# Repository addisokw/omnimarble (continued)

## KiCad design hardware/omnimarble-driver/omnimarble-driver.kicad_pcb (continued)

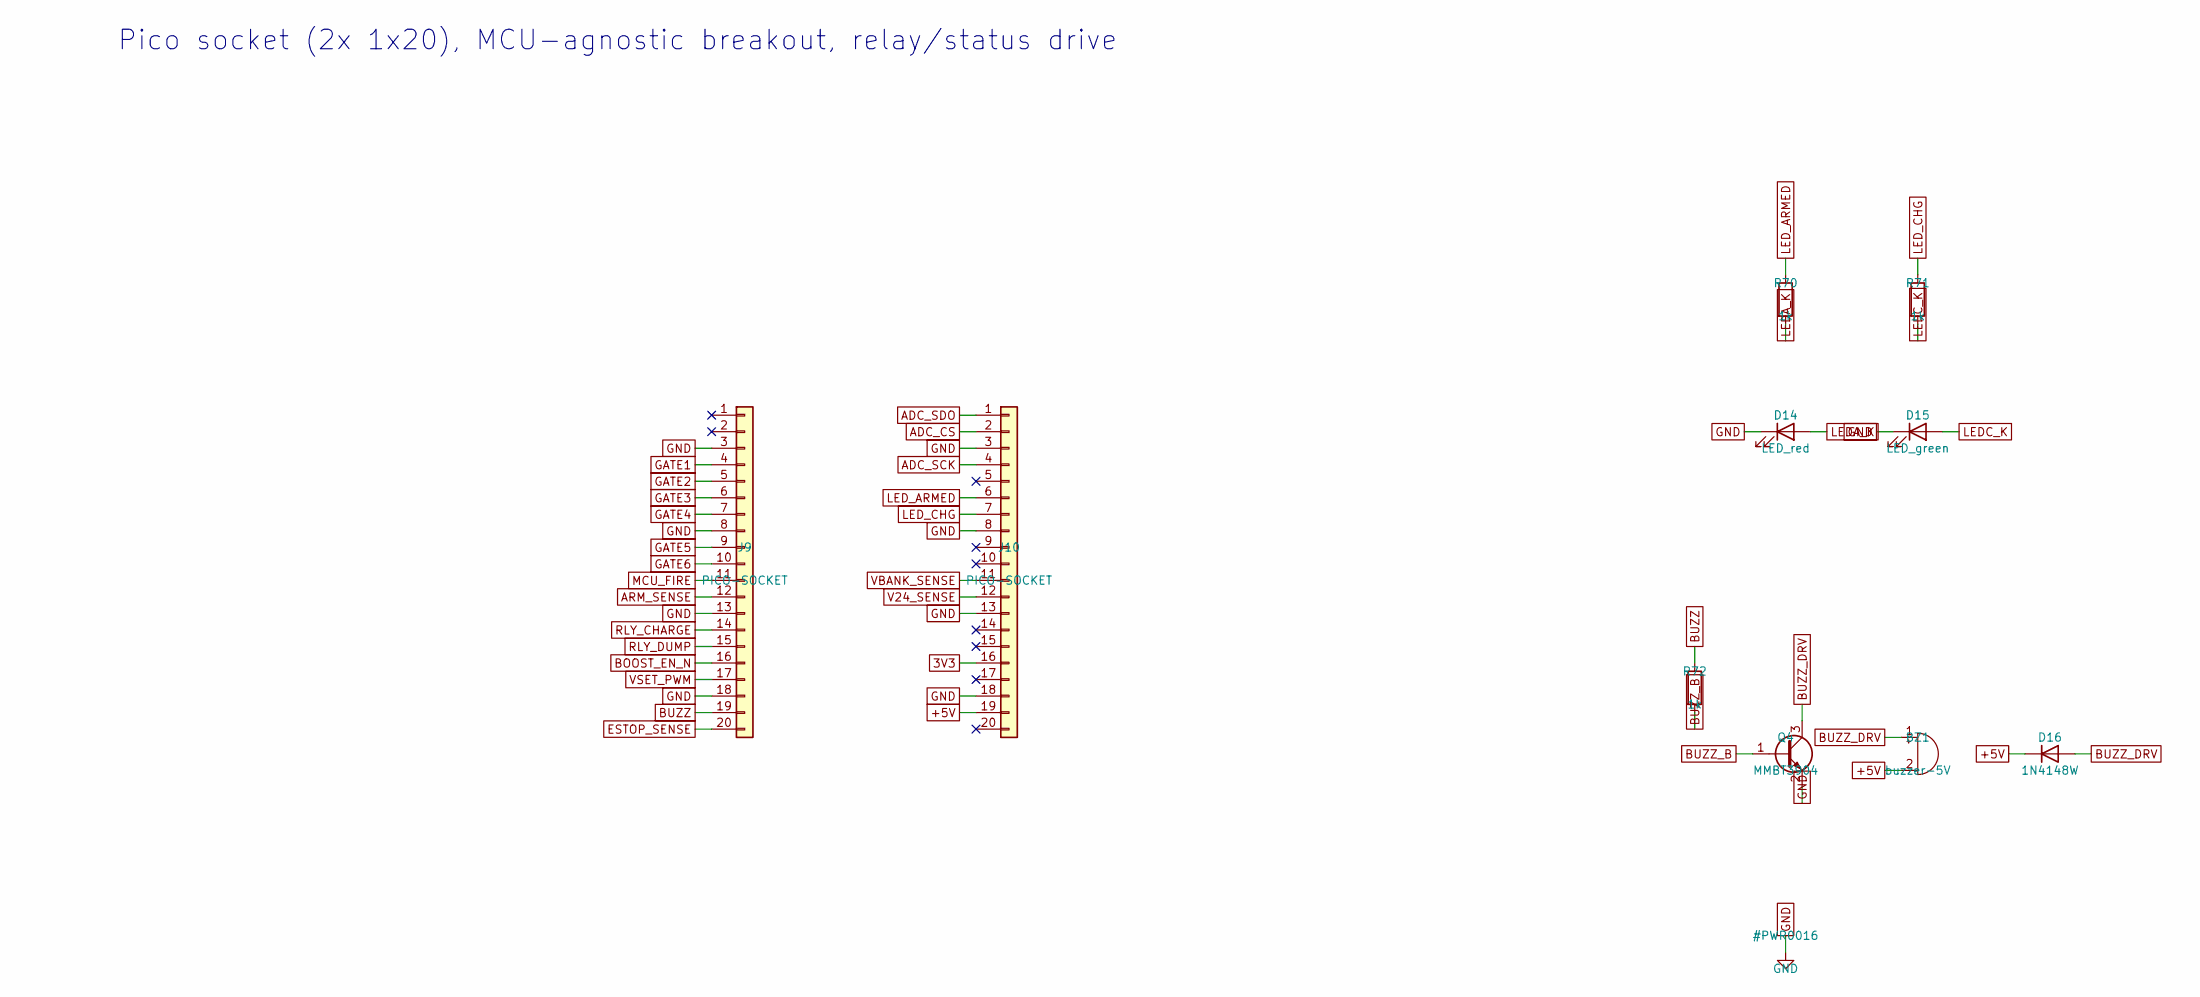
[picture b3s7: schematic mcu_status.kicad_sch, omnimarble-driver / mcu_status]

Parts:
BZ1: buzzer-5V; Buzzer_12x9.5RM7.6; LCSC C409842
D14: LED_red; LED_0603_1608Metric; LCSC C2286
D15: LED_green; LED_0603_1608Metric; LCSC C72043
D16: 1N4148W; D_SOD-123; LCSC C81598
J9, J10: PICO-SOCKET; PinSocket_1x20_P2.54mm_Vertical; LCSC C50984
Q4: MMBT3904; SOT-23; LCSC C20526
R70, R71, R72: 1k; R_0603_1608Metric; LCSC C21190

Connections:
3V3: J10.16; also elsewhere on the board
+5V: BZ1.2 (-), D16.1 (K), J10.19; also elsewhere on the board
ADC_CS: J10.2; also elsewhere on the board
ADC_SCK: J10.4; also elsewhere on the board
ADC_SDO: J10.1; also elsewhere on the board
ARM_SENSE: J9.12; also elsewhere on the board
BOOST_EN_N: J9.16; also elsewhere on the board
BUZZ: J9.19, R72.1
BUZZ_B: Q4.1 (B), R72.2
BUZZ_DRV: BZ1.1 (+), D16.2 (A), Q4.3 (C)
ESTOP_SENSE: J9.20; also elsewhere on the board
GATE1: J9.4; also elsewhere on the board
GATE2: J9.5; also elsewhere on the board
GATE3: J9.6; also elsewhere on the board
GATE4: J9.7; also elsewhere on the board
GATE5: J9.9; also elsewhere on the board
GATE6: J9.10; also elsewhere on the board
GND: D14.1 (K), D15.1 (K), J9.3, J9.8, J9.13, J9.18, J10.3, J10.8, J10.13, J10.18, Q4.2 (E); also elsewhere on the board
LEDA_K: D14.2 (A), R70.2
LEDC_K: D15.2 (A), R71.2
LED_ARMED: J10.6, R70.1
LED_CHG: J10.7, R71.1
MCU_FIRE: J9.11; also elsewhere on the board
RLY_CHARGE: J9.14; also elsewhere on the board
RLY_DUMP: J9.15; also elsewhere on the board
V24_SENSE: J10.12; also elsewhere on the board
VBANK_SENSE: J10.11; also elsewhere on the board
VSET_PWM: J9.17; also elsewhere on the board

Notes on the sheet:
Pico socket (2x 1x20), MCU-agnostic breakout, relay/status drive

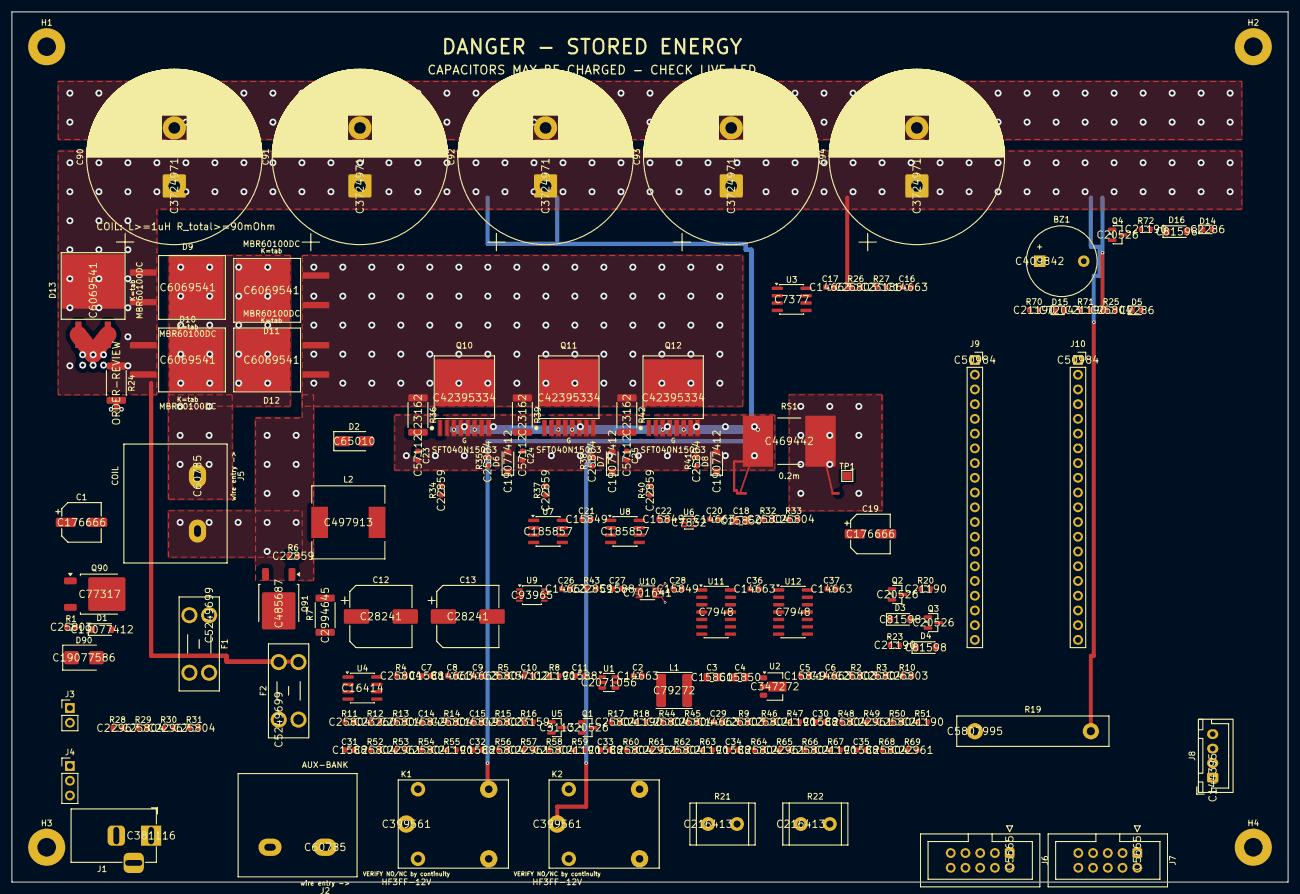
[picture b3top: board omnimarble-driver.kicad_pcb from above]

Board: 4 copper layers, 220.0 x 150.0 mm, 177 parts (0 on the bottom side), 95 nets.

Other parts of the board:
H1, H2, H3, H4: MountingHole_3.2mm_M3_Pad

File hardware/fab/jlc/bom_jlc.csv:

Comment,Designator,Footprint,LCSC Part #,Qty
10k,"R3,R4,R5,R11,R13,R14,R17,R29,R31,R32,R33,R35,R38,R41,R44,R45,R46,R48,R50,R52,R54,R56,R58,R60,R62,R64,R66,R68",R_0603_1608Metric,C25804,28
1k,"R8,R18,R20,R23,R47,R51,R55,R59,R63,R67,R70,R71,R72",R_0603_1608Metric,C21190,13
100n,"C2,C6,C8,C9,C16,C17,C20,C26,C29,C36,C37",C_0603_1608Metric,C14663,11
1n,"C7,C11,C27,C30,C31,C32,C33,C34,C35",C_0603_1608Metric,C1588,9
100k,"R1,R2,R9,R10,R15,R26",R_0603_1608Metric,C25803,6
1u,"C5,C14,C15,C21,C22,C28",C_0603_1608Metric,C15849,6
220k,"R49,R53,R57,R61,R65,R69",R_0603_1608Metric,C22961,6
10R,"R6,R34,R37,R40,R43",R_0603_1608Metric,C22859,5
MBR60100DC,"D9,D10,D11,D12,D13",D2PAK_MBR60100DC,C6069541,5
10n,"C10,C23,C24,C25",C_0603_1608Metric,C57112,4
BZT52C15,"D1,D6,D7,D8",D_SOD-123,C19077412,4
MMBT3904,"Q1,Q2,Q3,Q4",SOT-23,C20526,4
10u,"C3,C4,C18",C_0805_2012Metric,C15850,3
1N4148W,"D3,D4,D16",D_SOD-123,C81598,3
4.7R,"R36,R39,R42",R_2512_6332Metric,C25489,3
SFT040N150C3,"Q10,Q11,Q12",TOLL-8,C42395334,3
100R-10W,"R21,R22",R_Radial_Power_L11.0mm_W7.0mm_P5.00mm,C5110275,2
100u-35V,"C1,C19",CP_Elec_6.3x7.7,C176666,2
100u-63V,"C12,C13",CP_Elec_10x10.5,C28241,2
27k,"R28,R30",R_0603_1608Metric,C22967,2
HF3FF-12V,"K1,K2",Relay_HF3FF_T73,C399561,2
LED_red,"D5,D14",LED_0603_1608Metric,C2286,2
LM339,"U11,U12",SOIC-14_3.9x8.7mm_P1.27mm,C7948,2
UCC27524A,"U7,U8",SOIC-8_3.9x4.9mm_P1.27mm,C185857,2
0.15R-2512,R7,R_2512_6332Metric,C2903485,1
0.2m,RS1,Shunt_5930,C469442,1
10uH,L1,L_Changjiang_FNR6045S,C79272,1
24V-IN,J1,BarrelJack_Horizontal,C381116,1
4.3k,R16,R_0603_1608Metric,C23159,1
47R-5W,R19,R_Box_L26.0mm_W5.0mm_P20.00mm,C5807995,1
47k,R25,R_0603_1608Metric,C25819,1
47uH,L2,L_12x12mm_H8mm,C497913,1
5.1k,R27,R_0603_1608Metric,C23186,1
6.8k,R24,R_2512_6332Metric,C26073,1
74LVC1G08,U6,SOT-353_SC-70-5,C7832,1
78L12,U2,SOT-89-3,C347272,1
9.1k,R12,R_0603_1608Metric,C23260,1
ADS7042,U10,VSSOP-8_2.3x2mm_P0.5mm,C701641,1
AOD4185,Q90,TO-252-2,C5371006,1
AOD66923,Q91,TO-252-2,C485687,1
AP63205,U1,TSOT-23-6,C2071056,1
AUX-BANK,J2,TerminalBarrier_1x02_P9.50mm,C707836,1
COIL,J5,TerminalBarrier_1x02_P9.50mm,C707836,1
INA240A1,U9,TSSOP-8_3x3mm_P0.65mm,C93965,1
LED_green,D15,LED_0603_1608Metric,C2289,1
MCP6002,U3,SOIC-8_3.9x4.9mm_P1.27mm,C7377,1
RAIL-EMIT,J6,IDC-Header_2x05_P2.54mm_Vertical,C5665,1
RAIL-RECV,J7,IDC-Header_2x05_P2.54mm_Vertical,C5665,1
SMBJ26CA,D90,D_SMB,C113996,1
SPARE-JST,J8,JST_XH_B4B-XH-A_1x04_P2.50mm_Vertical,C144395,1
SS510,D2,D_SMA,C65010,1
TL431B,U5,SOT-23,C41283,1
UC3843B,U4,SOIC-8_3.9x4.9mm_P1.27mm,C2995531,1
buzzer-5V,BZ1,Buzzer_12x9.5RM7.6,C409842,1
